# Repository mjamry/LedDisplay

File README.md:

# LedDisplay
This is a simple project which aim was to create LED display.<br>
Whole display is made using three 8x8 LED matrixes which are driven by ATMEL ATiny2313 microcontroller.<br><br>

Main aim was to put whole display into small case (Z76) which dimensions are 60x110mm.

For more detailed description, schematics and PCBs take a look at wiki pages.

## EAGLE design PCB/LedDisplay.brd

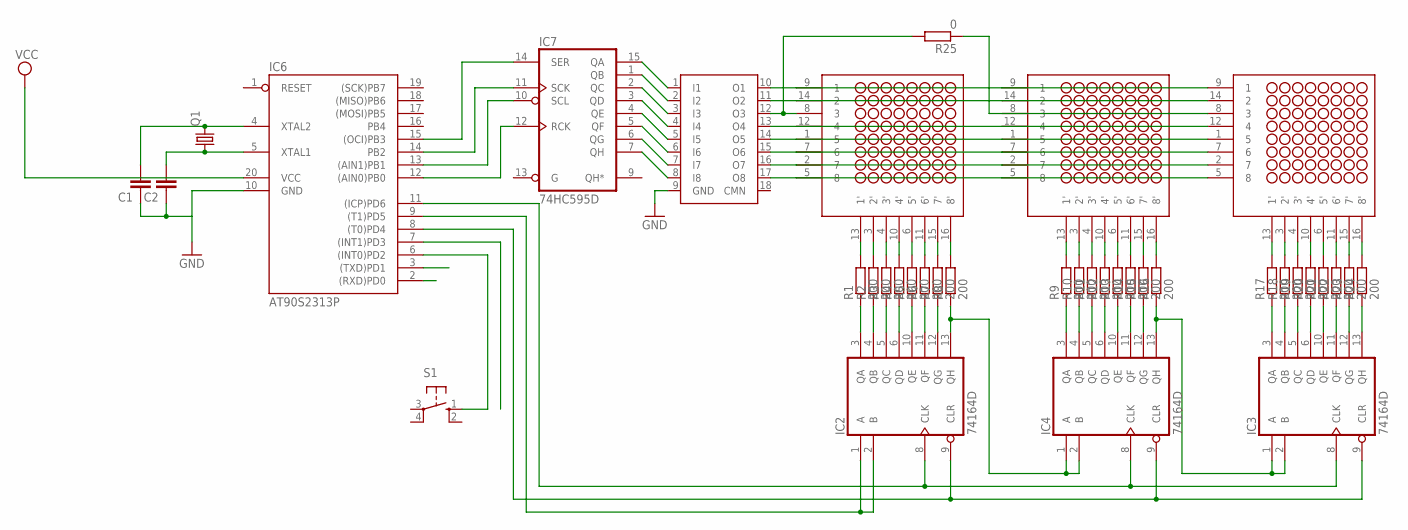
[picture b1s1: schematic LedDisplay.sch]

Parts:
C1, C2: C2,5-3; C2.5-3
IC2, IC3, IC4: 74164D; SO14
IC6: AT90S2313P; DIL20
IC7: 74HC595D; SO16
Q1: CRYSTALHC49U70; HC49U70
R1, R2, R3, R4, R5, R6, R7, R8, R9, R10, R11, R12, R13, R14, R15, R16, R17, R18, R19, R20, R21, R22, R23, R24: 200; M1206
R25: 0; M1206
S1: 10-XX; B3F-10XX
U$1, U$2, U$3: NFM-12881BG-11
U$4: ULN2803A; SO18W

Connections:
GND: C1.1, C2.1, IC2.7 (GND), IC3.7 (GND), IC4.7 (GND), IC6.10 (GND), IC7.8 (GND), U$4.9 (GND)
unnamed: IC7.7 (QH), U$4.8 (I8)
unnamed: IC7.6 (QG), U$4.7 (I7)
unnamed: IC7.5 (QF), U$4.6 (I6)
unnamed: IC7.4 (QE), U$4.5 (I5)
unnamed: IC7.3 (QD), U$4.4 (I4)
unnamed: IC7.2 (QC), U$4.3 (I3)
unnamed: IC7.1 (QB), U$4.2 (I2)
unnamed: IC7.15 (QA), U$4.1 (I1)
unnamed: R1.2, U$1.13 (1')
unnamed: R2.2, U$1.3 (2')
unnamed: R3.2, U$1.4 (3')
unnamed: R4.2, U$1.10 (4')
unnamed: R5.2, U$1.6 (5')
unnamed: R6.2, U$1.11 (6')
unnamed: R7.2, U$1.15 (7')
unnamed: R8.2, U$1.16 (8')
unnamed: IC2.3 (QA), R1.1
unnamed: IC2.4 (QB), R2.1
unnamed: IC2.5 (QC), R3.1
unnamed: IC2.6 (QD), R4.1
unnamed: IC2.10 (QE), R5.1
unnamed: IC2.11 (QF), R6.1
unnamed: IC2.12 (QG), R7.1
unnamed: IC2.13 (QH), IC4.1 (A), IC4.2 (B), R8.1
unnamed: R9.2, U$2.13 (1')
unnamed: R10.2, U$2.3 (2')
unnamed: R11.2, U$2.4 (3')
unnamed: R12.2, U$2.10 (4')
unnamed: R13.2, U$2.6 (5')
unnamed: R14.2, U$2.11 (6')
unnamed: R15.2, U$2.15 (7')
unnamed: R16.2, U$2.16 (8')
unnamed: IC4.3 (QA), R9.1
unnamed: IC4.4 (QB), R10.1
unnamed: IC4.5 (QC), R11.1
unnamed: IC4.6 (QD), R12.1
unnamed: IC4.10 (QE), R13.1
unnamed: IC4.11 (QF), R14.1
unnamed: IC4.12 (QG), R15.1
unnamed: IC3.1 (A), IC3.2 (B), IC4.13 (QH), R16.1
unnamed: R17.2, U$3.13 (1')
unnamed: R18.2, U$3.3 (2')
unnamed: R19.2, U$3.4 (3')
unnamed: R20.2, U$3.10 (4')
unnamed: R21.2, U$3.6 (5')
unnamed: R22.2, U$3.11 (6')
unnamed: R23.2, U$3.15 (7')
unnamed: R24.2, U$3.16 (8')
unnamed: IC3.3 (QA), R17.1
unnamed: IC3.4 (QB), R18.1
unnamed: IC3.5 (QC), R19.1
unnamed: IC3.6 (QD), R20.1
unnamed: IC3.10 (QE), R21.1
unnamed: IC3.11 (QF), R22.1
unnamed: IC3.12 (QG), R23.1
unnamed: IC3.13 (QH), R24.1
unnamed: C1.2, IC6.4 (XTAL2), Q1.2
unnamed: C2.2, IC6.5 (XTAL1), Q1.1
unnamed: IC2.9 (CLR), IC3.9 (CLR), IC4.9 (CLR), IC6.8 ((T0)PD4)
unnamed: IC2.1 (A), IC2.2 (B), IC6.9 ((T1)PD5)
unnamed: IC2.8 (CLK), IC3.8 (CLK), IC4.8 (CLK), IC6.11 ((ICP)PD6)
unnamed: IC6.6 ((INT0)PD2), S1.1 (S)
unnamed: U$1.9 (1), U$2.9 (1), U$3.9 (1), U$4.10 (O1)
unnamed: U$1.14 (2), U$2.14 (2), U$3.14 (2), U$4.11 (O2)
unnamed: R25.1, U$2.8 (3), U$3.8 (3)
unnamed: U$1.12 (4), U$2.12 (4), U$3.12 (4), U$4.13 (O4)
unnamed: U$1.1 (5), U$2.1 (5), U$3.1 (5), U$4.14 (O5)
unnamed: U$1.7 (6), U$2.7 (6), U$3.7 (6), U$4.15 (O6)
unnamed: U$1.2 (7), U$2.2 (7), U$3.2 (7), U$4.16 (O7)
unnamed: U$1.5 (8), U$2.5 (8), U$3.5 (8), U$4.17 (O8)
unnamed: IC6.12 ((AIN0)PB0), IC7.12 (RCK)
unnamed: IC6.13 ((AIN1)PB1), IC7.10 (SCL)
unnamed: IC6.14 (PB2), IC7.11 (SCK)
unnamed: IC6.15 ((OCI)PB3), IC7.14 (SER)
unnamed: R25.2, U$1.8 (3), U$4.12 (O3)
VCC: IC2.14 (VCC), IC3.14 (VCC), IC4.14 (VCC), IC6.20 (VCC), IC7.16 (VCC)

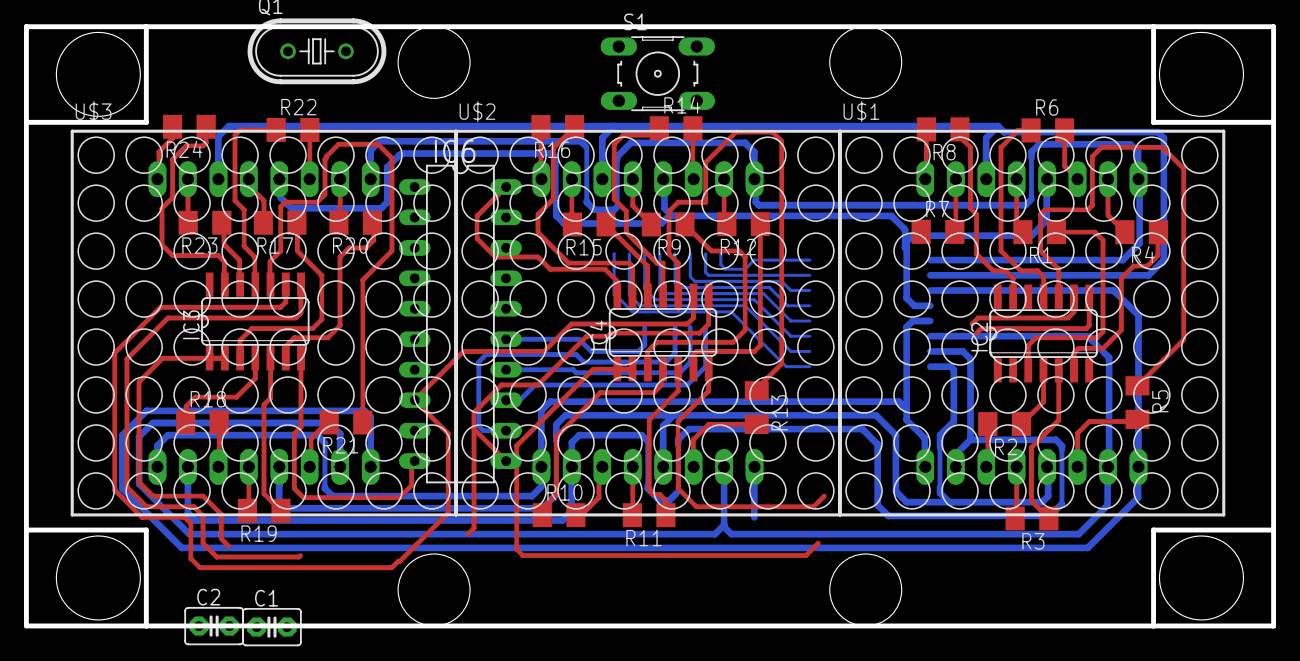
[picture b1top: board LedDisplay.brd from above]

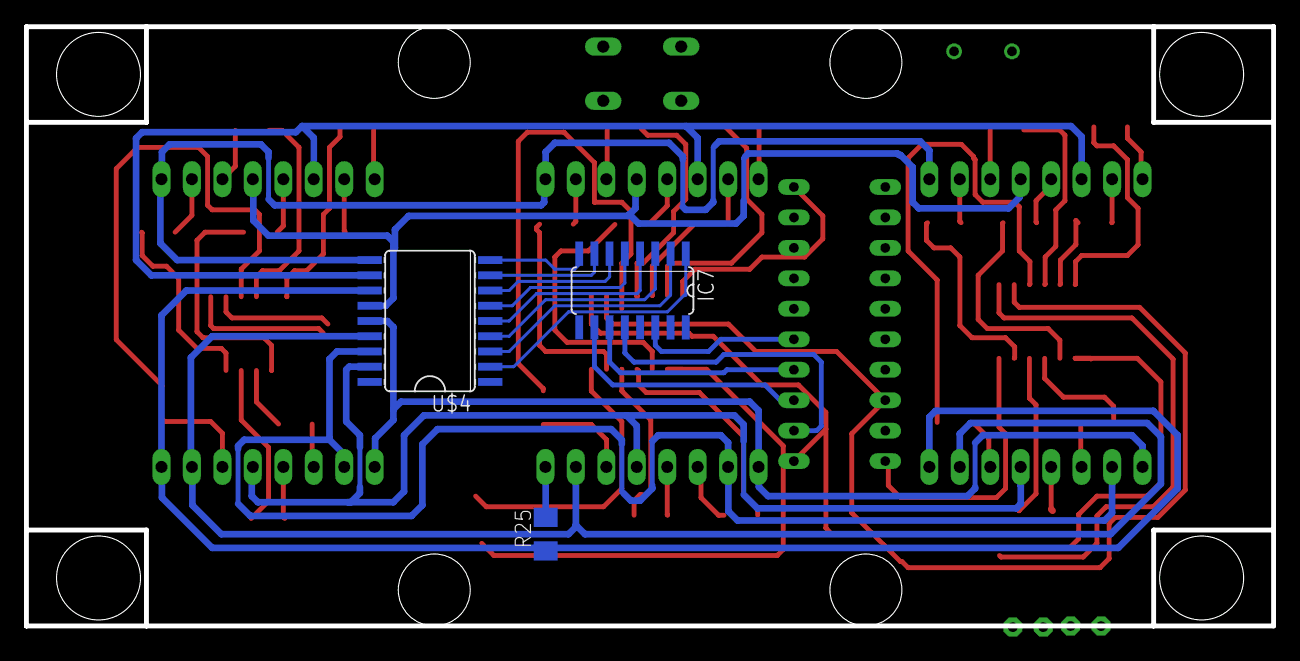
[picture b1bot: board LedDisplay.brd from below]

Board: 2 copper layers, 104.0 x 50.0 mm, 38 parts (3 on the bottom side), 77 nets.

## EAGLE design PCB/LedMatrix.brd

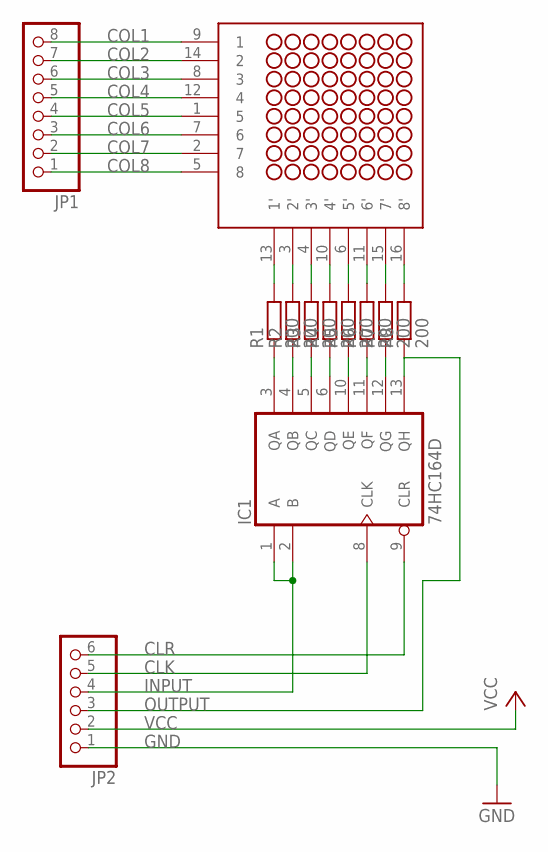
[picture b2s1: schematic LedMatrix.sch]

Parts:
IC1: 74HC164D; SO14
JP1: PINHD-1X8; 1X08
JP2: PINHD-1X6; 1X06
R1, R2, R3, R4, R5, R6, R7, R8: 200; R1206
U$1: NFM-12881BG-11

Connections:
CLK: IC1.8 (CLK), JP2.5
CLR: IC1.9 (CLR), JP2.6
COL1: JP1.8, U$1.9 (1)
COL2: JP1.7, U$1.14 (2)
COL3: JP1.6, U$1.8 (3)
COL4: JP1.5, U$1.12 (4)
COL5: JP1.4, U$1.1 (5)
COL6: JP1.3, U$1.7 (6)
COL7: JP1.2, U$1.2 (7)
COL8: JP1.1, U$1.5 (8)
GND: IC1.7 (GND), JP2.1
INPUT: IC1.1 (A), IC1.2 (B), JP2.4
unnamed: R1.2, U$1.13 (1')
unnamed: R2.2, U$1.3 (2')
unnamed: R3.2, U$1.4 (3')
unnamed: R4.2, U$1.10 (4')
unnamed: R5.2, U$1.6 (5')
unnamed: R6.2, U$1.11 (6')
unnamed: R7.2, U$1.15 (7')
unnamed: R8.2, U$1.16 (8')
unnamed: IC1.3 (QA), R1.1
unnamed: IC1.4 (QB), R2.1
unnamed: IC1.5 (QC), R3.1
unnamed: IC1.6 (QD), R4.1
unnamed: IC1.10 (QE), R5.1
unnamed: IC1.11 (QF), R6.1
unnamed: IC1.12 (QG), R7.1
OUTPUT: IC1.13 (QH), JP2.3, R8.1
VCC: IC1.14 (VCC), JP2.2

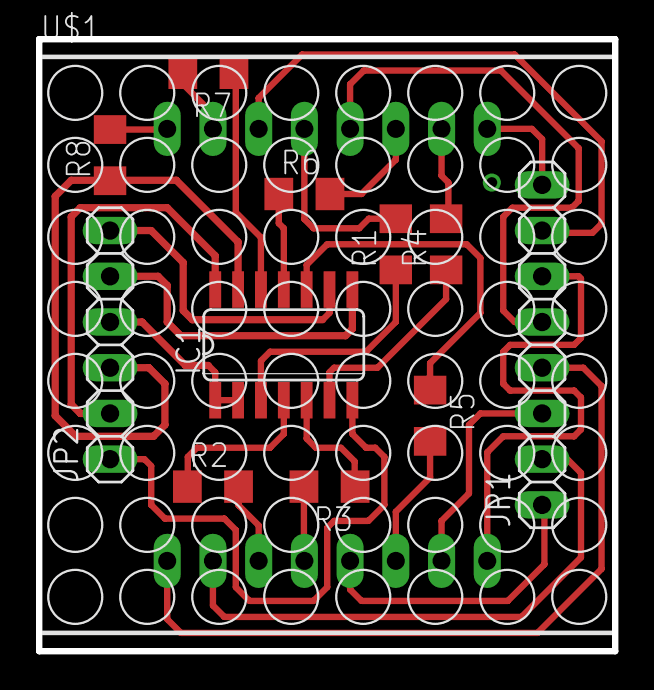
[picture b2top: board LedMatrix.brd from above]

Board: 2 copper layers, 32.0 x 34.0 mm, 12 parts (0 on the bottom side), 29 nets.

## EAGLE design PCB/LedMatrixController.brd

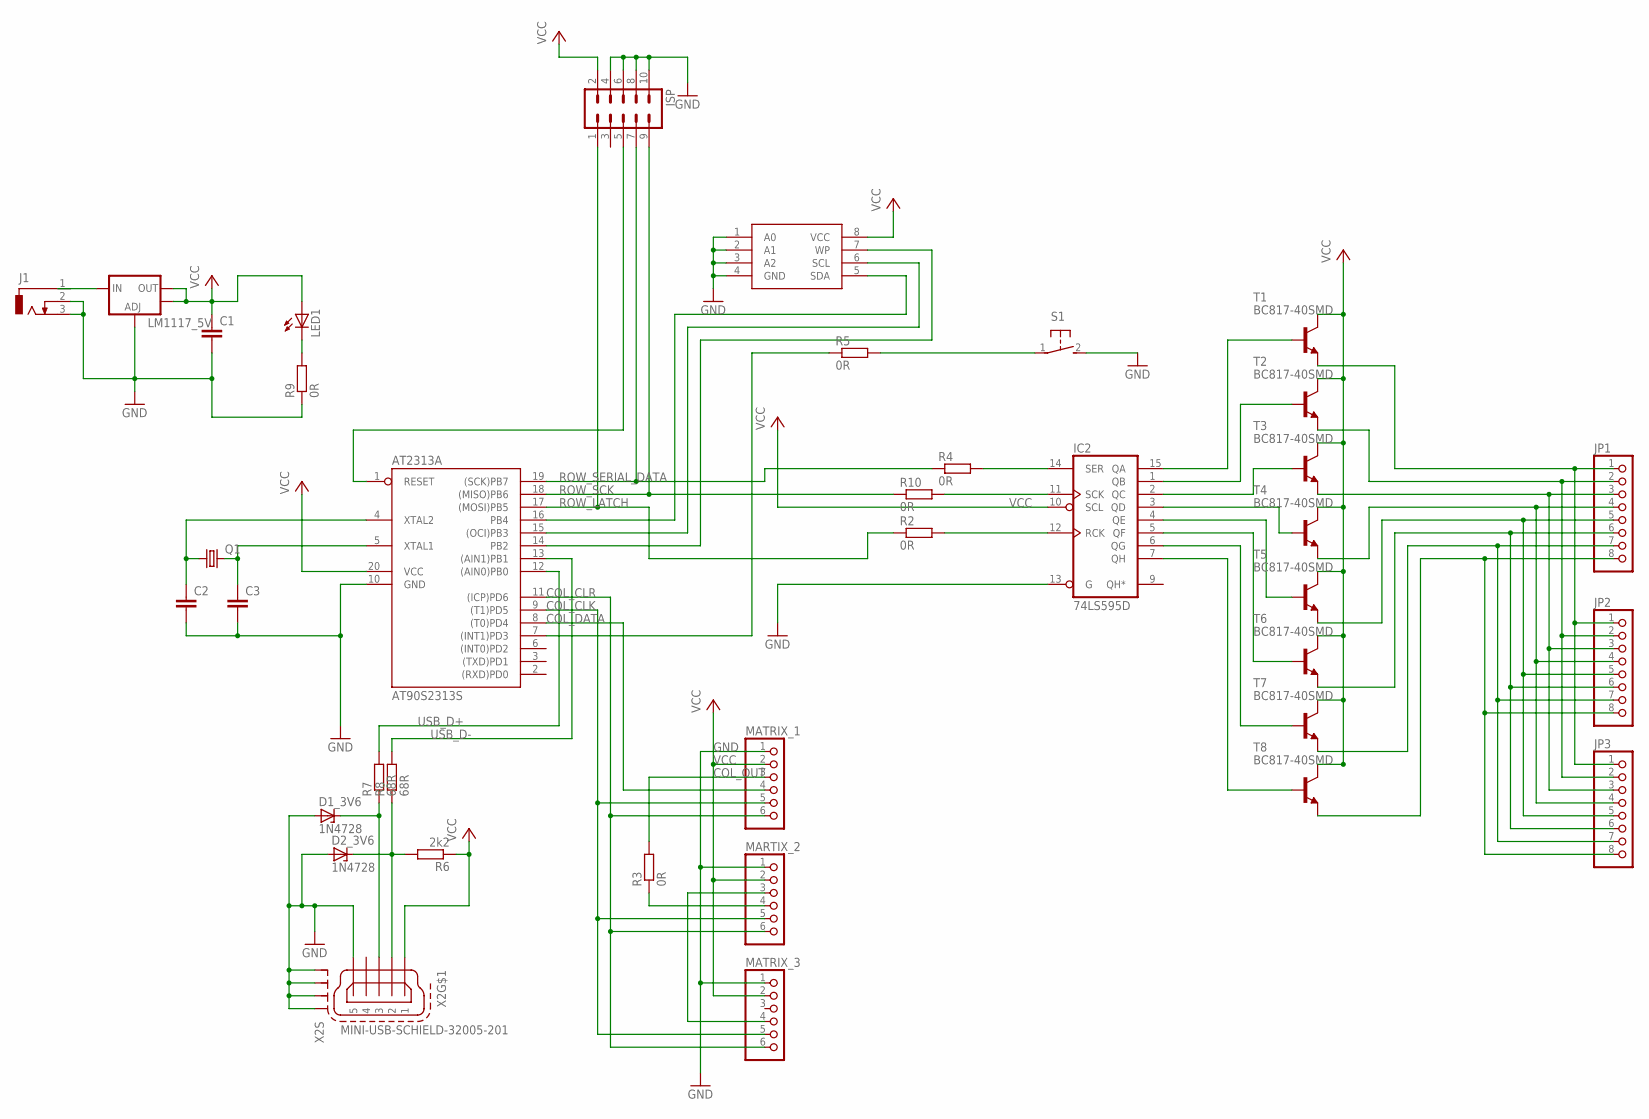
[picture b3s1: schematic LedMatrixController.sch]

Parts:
AT2313A: AT90S2313S; SO20L
C1: C-EU025-025X050; C025-025X050
C2, C3: C-EUC1206; C1206
D1_3V6, D2_3V6: 1N4728; DO41Z10
EEPROM: AT24C08; SO08
IC2: 74LS595D; SO16
ISP: ML10
J1: DCJ0303
JP1, JP2, JP3: PINHD-1X8; 1X08
LED1: LEDCHIPLED_1206; CHIPLED_1206
LM1117_5V: V_REG_LM1117SOT223; SOT223
MARTIX_2: PINHD-1X6; 1X06
MATRIX_1, MATRIX_3: PINHD-1X6; 1X06
Q1: CRYSTALHC49UP; HC49UP
R2, R3, R4, R5, R9, R10: 0R; R1206
R6: 2k2; R1206
R7, R8: 68R; R1206
S1: 31-XX; B3F-31XX
T1, T2, T3, T4, T5, T6, T7, T8: BC817-40SMD; SOT23-BEC
X2: MINI-USB-SCHIELD-32005-201; 32005-201

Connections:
+5V: IC2.16 (VCC)
COL_CLK: AT2313A.9 ((T1)PD5), MARTIX_2.5, MATRIX_1.5, MATRIX_3.5
COL_CLR: AT2313A.11 ((ICP)PD6), MARTIX_2.6, MATRIX_1.6, MATRIX_3.6
COL_DATA: AT2313A.8 ((T0)PD4), MATRIX_1.4
COL_OUT: MATRIX_1.3, R3.2
COL_OUT_2: MARTIX_2.4, R3.1
GND: AT2313A.10 (GND), C1.2, C2.2, C3.2, D1_3V6.A, D2_3V6.A, EEPROM.1 (A0), EEPROM.2 (A1), EEPROM.3 (A2), EEPROM.4 (GND), IC2.8 (GND), IC2.13 (G), ISP.4, ISP.6, ISP.8, ISP.10, J1.2, J1.3, LM1117_5V.1 (ADJ), MARTIX_2.1, MATRIX_1.1, MATRIX_3.1, R9.1, S1.2 (S), X2.5, X2.M1 (S1), X2.M2 (S2), X2.M3 (S3), X2.M4 (S4)
unnamed: AT2313A.4 (XTAL2), C2.1, Q1.1
unnamed: J1.1, LM1117_5V.3 (IN)
unnamed: AT2313A.5 (XTAL1), C3.1, Q1.2
unnamed: AT2313A.7 ((INT1)PD3), R5.1
unnamed: IC2.12 (RCK), R2.2
unnamed: AT2313A.16 (PB4), EEPROM.5 (SDA)
unnamed: IC2.14 (SER), R4.2
unnamed: MARTIX_2.3, MATRIX_3.4
unnamed: AT2313A.15 ((OCI)PB3), EEPROM.6 (SCL)
unnamed: IC2.11 (SCK), R10.2
unnamed: AT2313A.14 (PB2), EEPROM.7 (WP)
unnamed: AT2313A.1 (RESET), ISP.5
unnamed: R5.2, S1.1
unnamed: LED1.C, R9.2
R1: IC2.15 (QA), T1.B
R2: IC2.1 (QB), T2.B
R3: IC2.2 (QC), T3.B
R4: IC2.3 (QD), T4.B
R5: IC2.4 (QE), T5.B
R6: IC2.5 (QF), T6.B
R7: IC2.6 (QG), T7.B
R8: IC2.7 (QH), T8.B
ROW1: JP1.1, JP2.1, JP3.1, T1.E
ROW2: JP1.2, JP2.2, JP3.2, T2.E
ROW3: JP1.3, JP2.3, JP3.3, T3.E
ROW4: JP1.4, JP2.4, JP3.4, T4.E
ROW5: JP1.5, JP2.5, JP3.5, T5.E
ROW6: JP1.6, JP2.6, JP3.6, T6.E
ROW7: JP1.7, JP2.7, JP3.7, T7.E
ROW8: JP1.8, JP2.8, JP3.8, T8.E
ROW_LATCH: AT2313A.17 ((MOSI)PB5), ISP.1, R2.1
ROW_SCK: AT2313A.18 ((MISO)PB6), ISP.9, R10.1
ROW_SERIAL_DATA: AT2313A.19 ((SCK)PB7), ISP.7, R4.1
USB_D+: AT2313A.12 ((AIN0)PB0), R7.2
USB_D-: AT2313A.13 ((AIN1)PB1), R8.2
USB_DATA+: D1_3V6.C, R7.1, X2.3
USB_DATA-: D2_3V6.C, R6.2, R8.1, X2.2
VCC: AT2313A.20 (VCC), C1.1, EEPROM.8 (VCC), IC2.10 (SCL), ISP.2, LED1.A, LM1117_5V.2 (OUT), LM1117_5V.4 (OUT), MARTIX_2.2, MATRIX_1.2, MATRIX_3.2, R6.1, T1.C, T2.C, T3.C, T4.C, T5.C, T6.C, T7.C, T8.C, X2.1

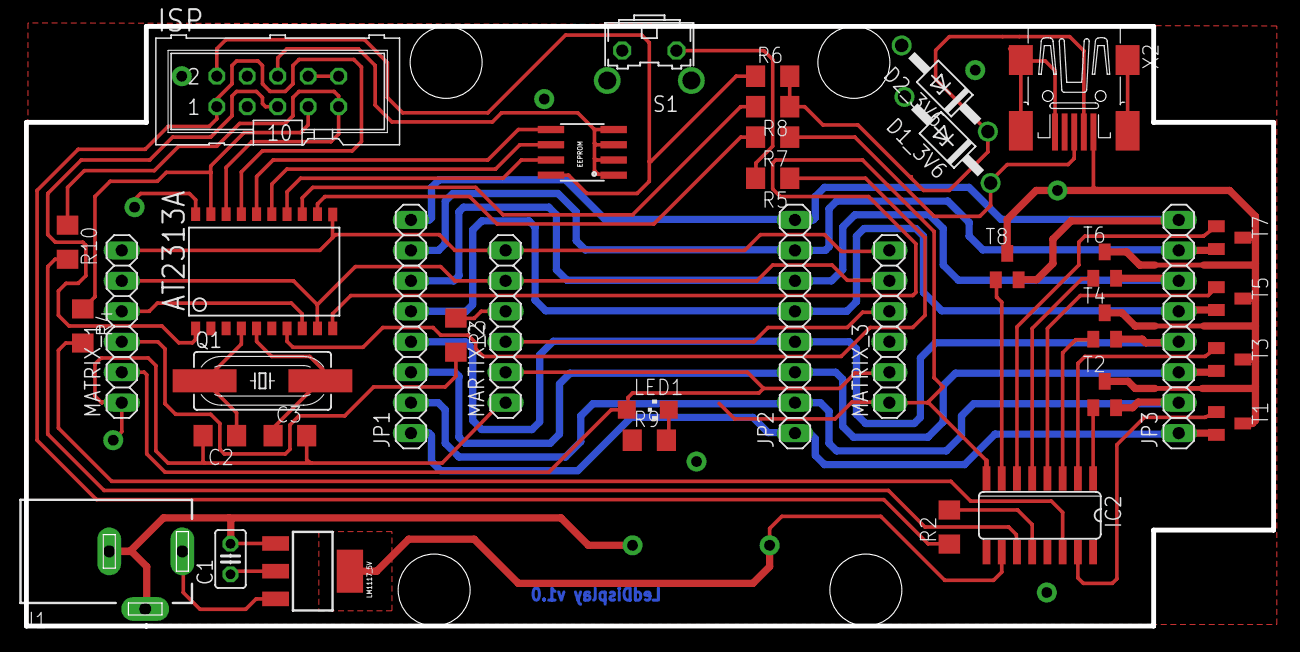
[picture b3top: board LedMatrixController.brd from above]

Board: 2 copper layers, 104.0 x 50.0 mm, 38 parts (0 on the bottom side), 44 nets.

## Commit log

2015-01-27 Added gitignore file with ignoring files for C projects.
2015-01-27 Initial version of application. Updated git ignore file according to files specific for avr prjects.
2015-01-27 Minor code clean up changes. Removed unwanted reset from the end of the loop.
2015-01-28 Added new character to display. Reset has been moved.
2015-01-29 Added timer1 channel A CTC mode interrupt handler. Also some additional code to test interupt.
2015-01-29 Added simple animation as a POF of using interrupts to drive animations.
2015-01-29 Minor changes in timer settings.
2015-01-29 Some part of initialisation have been moved to separate methods.
2015-01-29 Added header files. Const values have been moved to new header file.
2015-01-29 Renamed header file.
2015-01-29 Register clocking has been moved to separate function. Some minor code clean up changes.
2015-02-01 Added function which fills data from memory to have const length. Some minor code clean up changes.
2015-02-01 Added function to read data from memory. For the moment memory is simulated by array.
2015-02-01 Added PCB project with empty schematic file.
2015-02-01 Added basic elements to the schematics. Added dimensions and holes to the pcb.
2015-02-02 Updated pcb dimensions. Now is fits perfectly to the casing. Also some of the elements were changed to DIP packages.
2015-02-02 Another part of improvements in pcb layout, especially on the top layer.
2015-02-04 New versions of pcb. This time smaller one, just as a led controller.
2015-02-04 Added new pcb which main aim is to drive led matrixes. It will contains cpu, and power source.
2015-02-04 Added connections between main elements. Created dimensions on the pbc layout.
2015-02-04 Updated led matrix board.
2015-02-04 Minor corrections to the led matrix board.
2015-02-05 Minor measure corrections on the matrix board.
2015-02-05 Corrected positions of pinheads on the matrix controller board.
2015-02-05 Added support for latch shift register. First step.
2015-02-09 Another part of improvements in pcb layouts. Especially in pinhead area, to match both pcbs.
2015-02-09 Improvments in the top layer of matrix controller pcb. Added eeprom, connected power source and almost all IC.
2015-02-11 Added usb connector, and power led.
2015-02-11 Added descriptions to the lines on the ledMatrix board.
2015-02-14 Finished first version of the led matrix controller pcb
2015-02-19 Modified pinouts according to new wersion of the PCB. Modified delays to be more appropriate for 3 led martixes.
2015-02-19 Basic int1 handling by adding method to call during interrupt routine.
2015-02-20 Added fancy graphics to display on the led matrix
2015-03-03 Added button handling using external interrupt.
2015-03-03 ULN2803 has been replaced with NPN transistors

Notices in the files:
parts and their libraries:
led_matrix_8x8: This is v1 and is licensed under the Creative Commons (Attribution-Non-Commercial-Share Alike 2.0 UK)
SparkFun-PowerIC: Licensing: Creative Commons ShareAlike 4.0 International - https://creativecommons.org/licenses/by-sa/4.0
